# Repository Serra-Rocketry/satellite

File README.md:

# Helike — PocketQube Mission (#213 - LASC 2026)

PocketQube satellite project by **Serra Rocketry Team** for the Latin American
Space Challenge (LASC) 2026. Focus on bioinspired autorotating recovery system
(SRAB) and LoRa-based telemetry triangulation.

## Overview

The Helike satellite collects flight telemetry (IMU, barometric data, GPS)
and transmits it via LoRa radio at 915 MHz to a ground station. The payload
is a passive autorotating recovery system inspired by maple seed aerodynamics.

## Features

- BME280 environmental sensor (temperature, pressure, humidity)
- ICM-20602 6-axis IMU (accelerometer + gyroscope)
- NEO-8M GPS receiver (position, altitude, time)
- RFM95W LoRa radio (915 MHz, SF7, 125 kHz)
- SD card (primary) + LittleFS (fallback) data logging
- 18-field CSV telemetry packet format
- Vertical velocity computation (EMA filter)
- Automatic apogee detection
- Data validation (NaN + physical range checks)
- 5 Hz sample rate

## Hardware Requirements

| Component | Model | Interface |
|-----------|-------|-----------|
| MCU | ESP32-C3 Super Mini | - |
| Barometric | BME280 (or BMP280) | I2C (0x76) |
| IMU | ICM-20602 | I2C (0x69) |
| GPS | NEO-8M | UART (9600 baud) |
| Radio | RFM95W | SPI (915 MHz) |
| Storage | microSD card + LittleFS | SPI / flash |

## Software Requirements

- [PlatformIO](https://platformio.org/) (VS Code extension or CLI)
- Python 3.8+ (for analysis scripts in `extras/`)

Dependencies managed automatically by PlatformIO:

| Library | Version |
|---------|---------|
| sandeepmistry/LoRa | ^0.8.0 |
| Adafruit BME280 Library | ^2.2.4 |
| Adafruit BMP280 Library | ^2.6.8 |
| TinyGPSPlus | ^1.0.3 |

## Quick Start

### 1. Build the Firmware

```bash
pio run -e helike_esp32c3
```

### 2. Upload to Satellite

```bash
pio run -e helike_esp32c3 -t upload --upload-port /dev/ttyACM0
```

### 3. Monitor Serial Output

```bash
pio device monitor -b 115200
```

### 4. Run Unit Tests

```bash
pio test -e native
```

## Repository Structure

```text
satellite/
├── src/                       # Main firmware source
│   ├── main.cpp               # Entry point (setup + loop)
│   ├── config.h               # Global configuration
│   ├── sensors/               # Sensor drivers (ISensor interface)
│   │   ├── BME280Sensor.h/.cpp
│   │   ├── ICM20602Sensor.h/.cpp
│   │   └── GPSSensor.h/.cpp
│   └── modules/               # System modules
│       ├── LoRaModule.h/.cpp
│       ├── TelemetryModule.h/.cpp
│       ├── FilesystemModule.h/.cpp
│       ├── LEDModule.h/.cpp
│       └── BuzzerModule.h/.cpp
├── lib/calc/                  # Header-only calculation library
│   ├── SensorData.h
│   ├── VerticalVelocity.h
│   ├── ApogeeDetection.h
│   └── DataValidation.h
├── test/                      # Native unit tests (Unity)
│   ├── test_vz/
│   ├── test_apogee/
│   └── test_validation/
├── test_hardware/             # Hardware validation sketches
│   ├── sensor/                # Isolated sensor tests
│   ├── integration/           # Multi-sensor integration
│   └── storage/               # Filesystem tests
├── docs/                      # Documentation
│   ├── software.md
│   ├── hardware.md
│   ├── firmware.md
│   ├── flowchart.md
│   └── adr/                   # Architecture Decision Records
├── extras/
│   └── wing-analysis/         # SRAB aerodynamic study
├── hardware/                  # CAD and PCB files
└── platformio.ini             # PlatformIO configuration
```

## Documentation

| Document | Description |
|----------|-------------|
| [Software Architecture](docs/software.md) | Module structure, data flow, validation |
| [Hardware Specs](docs/hardware.md) | Pinout, sensors, LoRa configuration |
| [Firmware Guide](docs/firmware.md) | Build, upload, testing, debug |
| [Flowcharts](docs/flowchart.md) | System diagrams (Mermaid) |
| [ADRs](docs/adr/) | Architecture Decision Records |
| [Hardware Tests](test_hardware/docs/) | Bench guides and checklists |
| [Wing Analysis](extras/wing-analysis/docs/) | SRAB aerodynamics |

## Development Workflow

1. Validate individual sensors in `test_hardware/sensor/`
2. Run integration tests in `test_hardware/integration/`
3. Execute unit tests: `pio test -e native`
4. Run aerodynamic studies: `extras/wing-analysis/`
5. Consolidate results in technical documentation
6. Integrate final firmware

## Quality Tools

```bash
# Markdown linting
npx -y markdownlint-cli "README.md" "docs/**/*.md" "test_hardware/docs/**/*.md" "extras/**/*.md" "hardware/**/*.md"

# Native unit tests
pio test -e native
```

## License

MIT License — see LICENSE file for details.

## Team

**Serra Rocketry Team** — Missão Helike (#213 - LASC 2026)

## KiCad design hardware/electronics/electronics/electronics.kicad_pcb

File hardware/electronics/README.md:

# Electronics Hardware

This directory contains the electrical design files for the Helike satellite, including schematics and PCB layouts.

## Project Structure

```text
electronics/
├── electronics.kicad_pro   # KiCad project file
├── electronics.kicad_sch   # Circuit schematic
├── electronics.kicad_pcb    # PCB layout
├── electronics.pretty/      # Custom footprints
└── Library.pretty/         # Local component library
```

## Design Notes

- **MCU**: ESP32-C3 Super Mini
- **Interface**: I2C for sensors, SPI for LoRa and SD Card, UART for GPS.
- **Tools**: Designed using KiCad 8.0.

For the mechanical integration of the PCB, see `hardware/mechanical/electronics/`.

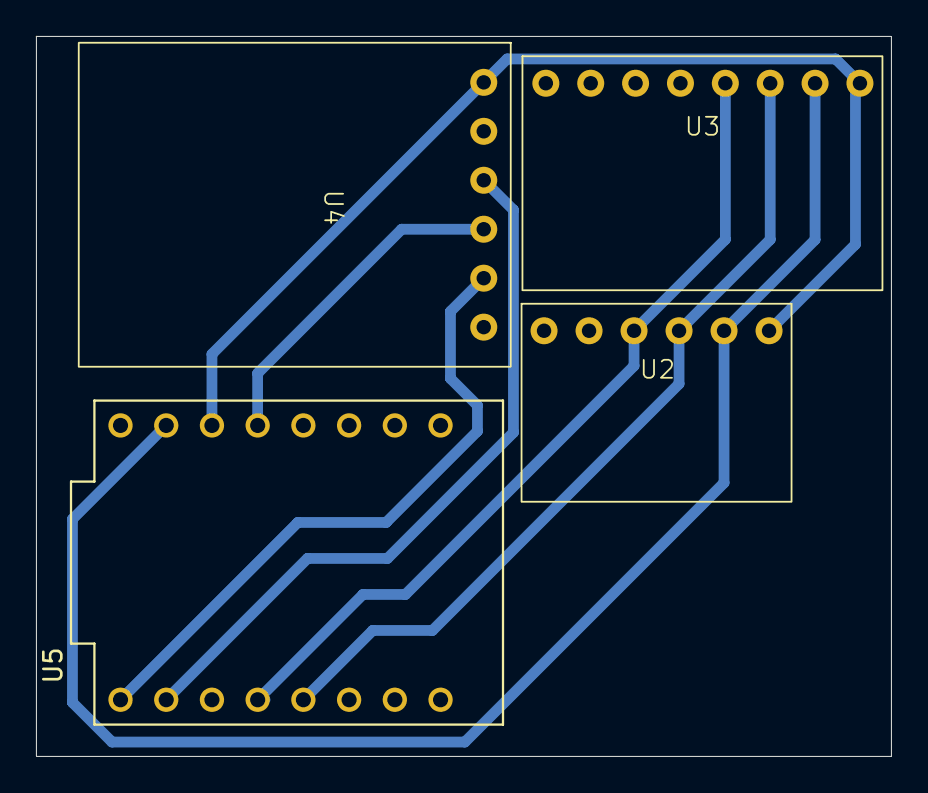
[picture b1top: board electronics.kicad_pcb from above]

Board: 2 copper layers, 47.5 x 40.0 mm, 4 parts (0 on the bottom side), 8 nets.

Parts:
U2: BME280
U3: ICM-20602
U4: SD Card mini module
U5: ESP32-C3 SUPERMINI; MODULE_ESP32-C3_SUPERMINI_TH

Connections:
/3.3 VCC: U2.1 (VCC), U3.1 (VCC), U4.1 (VCC), U5.3.3 (3V3)
/CLK_SD: U4.4 (CLK), U5.4 (GPIO4)
/CS_SD: U4.2 (CS), U5.10 (GPIO10)
/GND: U2.2 (GND), U3.2 (GND), U4.6 (GND), U5.G (GND)
/MISO: U4.5 (MISO), U5.5 (GPIO5)
/MOSI: U4.3 (MOSI), U5.6 (GPIO6)
/SCL: U2.3 (SCL), U3.3 (SCL), U5.9 (GPIO9)
/SDA: U2.4 (SDA), U3.4 (SDA), U5.8 (GPIO8)

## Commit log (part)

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2026-04-08 [WINGS] Add reverse DXF analysis script
    - New script analisar_dxf.py: extract wing geometry from DXF and run descent simulations
    - Supports SPLINE, POLYLINE, and LINE entities from CAD files
    - Analyzes chord distribution and calculates optimal configurations
    - Outputs geometry plots, JSON data, and text reports
    Tested with Asa2.DXF:
    - Extracts 125mm radius wing with complex geometry
2026-04-08 [WINGS] Fix DXF analysis: proper spline interpolation and area calculation
    Fixed two critical issues:
    1. Contour interpolation: Use scipy.interpolate.splprep/splev to properly
    interpolate spline curves instead of using raw control points
    Result: 34 points → 340 smooth points ✓
    2. Area calculation: Use Polygon (Shapely) with Shoelace formula for
    accurate area instead of simple trapezoid integration
2026-04-08 [DOCS] Add DXF analysis documentation
    Complete guide for reverse workflow: CAD → DXF → Analysis
    Includes:
    - Workflow diagram
    - Usage instructions
    - Algorithm explanation
    - Configuration parameters
2026-04-08 fix: Corrigir física da simulação de descida
    - Implementar fórmula aerodinâmica correta: v = √(2*m*g / (ρ*Cd*A))
    - Remover fórmula empírica incorreta que não respondia à área
    - Aceitar area_real_cm2 como parâmetro (extraída do DXF via Shapely)
    - Remover recálculo duplicado de área por integração
    - Adicionar constantes físicas explícitas (ρ_ar, Cd)
    - Validação: aumentar área 9x reduz v_terminal em 66.5% (√9 ≈ 1/3)
2026-04-08 feat: Adicionar arrasto da área frontal do PocketQube
    - Adicionar área frontal do PocketQube (50×50 mm = 25 cm²) ao cálculo
    - Fórmula: A_total = n_asas × area_asa + area_frontal_pq
    - Impacto: velocidade reduz ~6-16% dependendo do número de asas
    - Validação com Asa2:
    * 2 asas: 32.78 → 27.64 m/s (-15.7%)
    * 4 asas: 23.31 → 21.25 m/s (-8.8%)
2026-04-08 fix: Atualizar estudos de asas com fórmula aerodinâmica correta
    - Atualizar estudo_asa_2p.py com v_terminal aerodinâmica (v = √(2mg/ρCdA))
    - Atualizar estudo_asa_helike.py com v_terminal aerodinâmica
    - Adicionar área frontal do PocketQube (25 cm²) em ambos
    - Corrigir ordem de operações em cálculo de massa por asa (helike.py)
    - Documentar unidades claramente (R em metros)
    - Adicionar aviso sobre calibração de área (modelo 0.03*R² subestima ~4x)
2026-04-08 feat: Copy OpenCode ecosystem from flight-computer to satellite project
    - Add complete .opencode directory structure with OpenCode configuration
    - Copy and adapt opencode.yaml for Satellite project
    - Import 6 specialized skills: embedded-architect, firmware-developer, fsm-specialist, code-reviewer, test-engineer, documentation-specialist
    - Copy TEAM.md with team structure and RACI matrix
    - Copy SKILLS_INDEX.md for skill documentation
    - Add package.json and .gitignore for OpenCode compatibility
2026-04-08 test: Teste 2 - Sensores unificados e BMP280 com SPIFFS
    Adicionados arquivos de teste para integração de sensores:
    - sensores_unificado.ino: Integra ICM20602 (acelerômetro/giroscópio) + BMP280 (pressão/altura)
    - bmp280_spiffs.ino: Teste isolado de BMP280 com salvamento em SPIFFS
    Status do Teste 2 (08/04/2026):
    - RESULTADO: Satélite perdido durante o voo
    - PROBLEMA: Telemetria não funcionou - não conseguimos ativar a comunicação LoRa
2026-04-08 Add more test files
2026-04-09 fix: Ajustar I2C no ESP32-C3 e adicionar checklist de bancada
2026-04-09 chore: Consolidar sketches de teste em subdiretorios
2026-04-09 refactor: atualizar README para formato 1P com ESP32-C3 single-core
    - Trocar satélite de ESP32 DevKit V1 (dual-core) para ESP32-C3 Super Mini (single-core)
    - Adicionar formato final 1P com restrições de tamanho e potência
    - Reescrever arquitetura multi-core → single-core com scheduler cooperativo
    - Elevar 'Estudo do Freio Aerodinâmico' para Fase 1 (foco inicial)
    - Atualizar pinouts para ESP32-C3 (13 pinos em vez de 34)
    - Revisar cronograma de marcos com foco em freio samara
2026-04-09 docs: adicionar detalhes sobre código embarcado dos testes de queda
    Documentar progresso em desenvolvimento:
    - Eletrônica: Circuito I2C com ICM-20602 + BMP280 testado e validado
    - Código embarcado: 690 linhas em 5 arquivos Arduino com testes completos
    * sensores_unificado.ino: Integração completa com logging em CSV
    * Detecção automática de sensores, reset I2C, tratamento de erros
    * Leitura raw com conversão para unidades físicas (m/s², rad/s, Pa, m)
2026-04-09 docs: análise técnica detalhada do código de testes de queda
    Adicionar documento de análise do sensores_unificado.ino:
    - Visão geral: 274 linhas integrando ICM-20602 + BMP280
    - Pontos fortes: suporte multi-plataforma, I2C raw, CSV estruturado
    - 8 áreas de melhoria identificadas com prioridades
    - Recomendações críticas:
    * Cálculo de taxa de descida (dh/dt)
2026-04-09 feat: versão melhorada do código de testes de queda (sensores_unificado_v2)
    Implementação das recomendações críticas da análise técnica:
    Melhorias de Taxa de Aquisição:
    - 500ms → 50ms (20 Hz instead of 2 Hz)
    - Melhor captura de eventos dinâmicos em queda
    Cálculo de Velocidade Vertical (NOVO):
    - Implementa dh/dt com filtro de suavização
2026-04-09 docs: guia completo de implementação dos testes de queda (Fase 1.3)
    Adicionar documento de 350+ linhas com procedimentos detalhados:
    Hardware & Setup:
    - Lista de componentes necessários
    - Pinagem para ESP32-C3
    - Estrutura mecânica de suporte
    Protocolo de Testes em 4 Fases:
2026-04-09 docs: adicionar README na pasta test/ para documentar testes
    Criar guia de navegação completo para testes:
    - Estrutura de diretórios com descrição
    - Propósito de cada teste (6 arquivos Arduino)
    - Status: ✅ 3 documentos de teste criados/atualizados
    - Recomendações por fase do projeto
    - Setup rápido com hardware pinout
2026-04-09 feat: Integrar GPS NEO-8M, BME280 com umidade e criar testes completos (v3)
    - Substituir BMP280 + AHT por BME280 (barômetro + termômetro + higrômetro integrado)
    - Adicionar GPS NEO-8M via UART com parser NMEA completo
    - Criar sensores_unificado_v3.ino com integração ICM-20602 + BME280 + GPS
    - Criar teste isolado gps_neo8m.ino com suporte completo a sentencas GPRMC/GPGGA/GPGSA
    - Criar teste isolado bme280_completo.ino com cálculos de ponto de orvalho e índice de calor
    - Atualizar README.md com novos componentes e pinouts
2026-04-09 docs: Adicionar QUICK_START_V3.md com guia rápido de testes
    - Instruções de instalação de bibliotecas
    - Pinagem para cada teste (GPS, BME280, v3 integrado)
    - Exemplos de saída Serial esperada
    - Tabela de troubleshooting rápido
    - Fluxo recomendado de testes
    - Referência de #defines importantes
2026-04-09 fix: Reconciliar inconsistências no plano de testes de queda e harmonizar documentação
    - Corrigir conflito v_terminal (23.31 m/s vs -5 m/s): esclarecer que testes em 10m NÃO atingem regime terminal
    - Redefinir metodologia de análise: usar Vz_médio em janela estável vs Vz_min (mais robusto para quedas curtas)
    - Remover todas referências a BMP280/AHT10/MPU6050 do README (agora BME280/ICM-20602 em Fases 4-6)
    - Adicionar checklist crítico de validação de hardware: níveis lógicos GPS TX, alimentação dual 3.3V/5V, pull-ups I2C
    - Atualizar tabela de testes com valores reais de simulação do Asa2_relatorio.txt
    - Melhorar documentação de pinagem e protocolos de teste
2026-04-17 feat: aprimorar simulador samara e documentar uso
2026-04-17 chore: registrar demais alterações e artefatos de análise
2026-04-17 add test files
2026-04-18 chore: reorganizar documentação do repositório e padronizar lint markdown
2026-05-05 Switch from LittleFS to SD for file handling
    mi!
2026-05-06 Refactor file handling and improve file naming
    mi!2
2026-05-06 Refactor data logging and file name generation
2026-05-06 Add SD/SPIFFS fallback test for BMP280
2026-05-08 Update CDB.kicad_prl configuration settings
2026-05-08 Update fp-info-cache
2026-05-12 reorganizar diretorios test/ e extras/ e migrar SPIFFS para LittleFS
    - test/: dividido em docs/, sensor/, integration/, storage/
    - extras/wing-analisys/: src/, geometry/, results/, docs/, guides/
    - SD_SPIFFS_fallback migrado para sd_littlefs_fallback (LittleFS)
    - bmp280_spiffs renomeado para bmp280_littlefs
    - paths atualizados em todos os documentos afetados
2026-05-12 documentar lib/calc, testes nativos Unity e reorganizar docs
    - Adicionar Doxygen comments nos headers lib/calc/
    - Escrever 25 testes unitarios nativos (Vz, apogeu, validacao)
    - Atualizar README.md, AGENTS.md, docs/software.md, docs/README.md
    - Mover hardware sketches para test_hardware/ (fora do pio test)
    - Atualizar paths e remover referencias a SPIFFS nos docs
2026-05-12 adicionar .gitignore e remover opencode/lock do tracking
    - Ignorar .opencode/, .obsidian/, .pio/, venv/, __pycache__,
    hardware/CDB/.history/, *.lck, .DS_Store, *.swp
    - Remover .opencode/ do git (mantido local)
    - Remover ~CDB.kicad_sch.lck do git (arquivo temporario)
2026-05-13 simplificar para plataforma unica ESP32-C3 Super Mini
    - Remover referencias ao ESP32 DevKit V1 (satellite)
    - Remover envs satellite_esp32 e beacon_esp32c3 do platformio.ini
    - Atualizar pinagem, arquitetura e comandos de build nos docs
2026-06-08 bak commit
2026-06-10 test 10-06
2026-06-18 Add test 4 simulations with safety factor and test analysis script
2026-06-23 rocketpy integration
2026-06-24 Revert "rocketpy integration"
    This reverts commit 52f25b94c023dc15a0fb60d644f114ca0d5aef4b.
2026-06-24 Reapply "rocketpy integration"
    This reverts commit 802c1b2bb8e844ed6fbd85728b67b4cd0f4489f9.
2026-06-24 Remove PDFs de artigos (copyright) - mantem scripts e resultados
2026-06-24 Adiciona PDFs de artigos ao .gitignore
2026-06-24 docs: reestrutura documentacao completa do satellite
    - README.md: atualiza estrutura de docs (software, firmware, hardware, flowchart)
    - flowchart.md: adiciona fluxos runtime, dados, storage, iniciacao e desenvolvimento
    - hardware.md: reespecifica pinagem, diagrama de blocos, alimentacao, storage
    - software.md: adiciona arquitetura, formato telemetria CSV, storage fallback, recursos
    - firmware.md: documentacao detalhada de cada modulo (main, sensores, comunicacao)
    - CHANGELOG.md: registro de versoes (1.0.0 e 1.1.0)
2026-06-24 refactor: adiciona headers Doxygen e expande SensorData no lib/calc
    - ApogeeDetection.h: header Doxygen completo, pragma once, endif
    - DataValidation.h: header Doxygen, pragma once, endif
    - VerticalVelocity.h: header Doxygen, pragma once, endif, corrige formula EMA
    - SensorData.h: adiciona campos temperatura, umidade, lat, lon, altura_gps, satellites
    - test_validation.cpp: atualiza makeData para novos campos, ajusta thresholds
2026-06-24 chore: ajusta configuracao de build e IDE
    - platformio.ini: adiciona SRC filter, SERIAL_USB_BUFFER_SIZE, -Ilib
    - c_cpp_properties.json: adiciona flags USB e Serial para ESP32-C3
    - opencode.json: remove provider local GGUF (mantem schema)
2026-06-24 feat: adiciona firmware do satellite (main, sensores, modulos)
    - main.cpp: setup + loop com BME280, ICM-20602, GPS, LoRa, Serial
    - config.h: pinos, thresholds, intervalos
    - sensors/: BME280Sensor, ICM20602Sensor, GPSSensor
    - modules/: LoRaModule, BuzzerModule, LEDModule, TelemetryModule, FilesystemModule
2026-06-24 docs: adiciona registros de decisoes arquiteturais (ADR)
    - 001-no-fsm-no-sleep: justifica ausencia de FSM e modo sleep
    - 002-sd-littlefs-fallback: estrategia de storage com fallback
    - 003-tinygpsplus-vs-manual: escolha do TinyGPSPlus
    - 004-platformio-vs-arduino-ide: escolha do PlatformIO
